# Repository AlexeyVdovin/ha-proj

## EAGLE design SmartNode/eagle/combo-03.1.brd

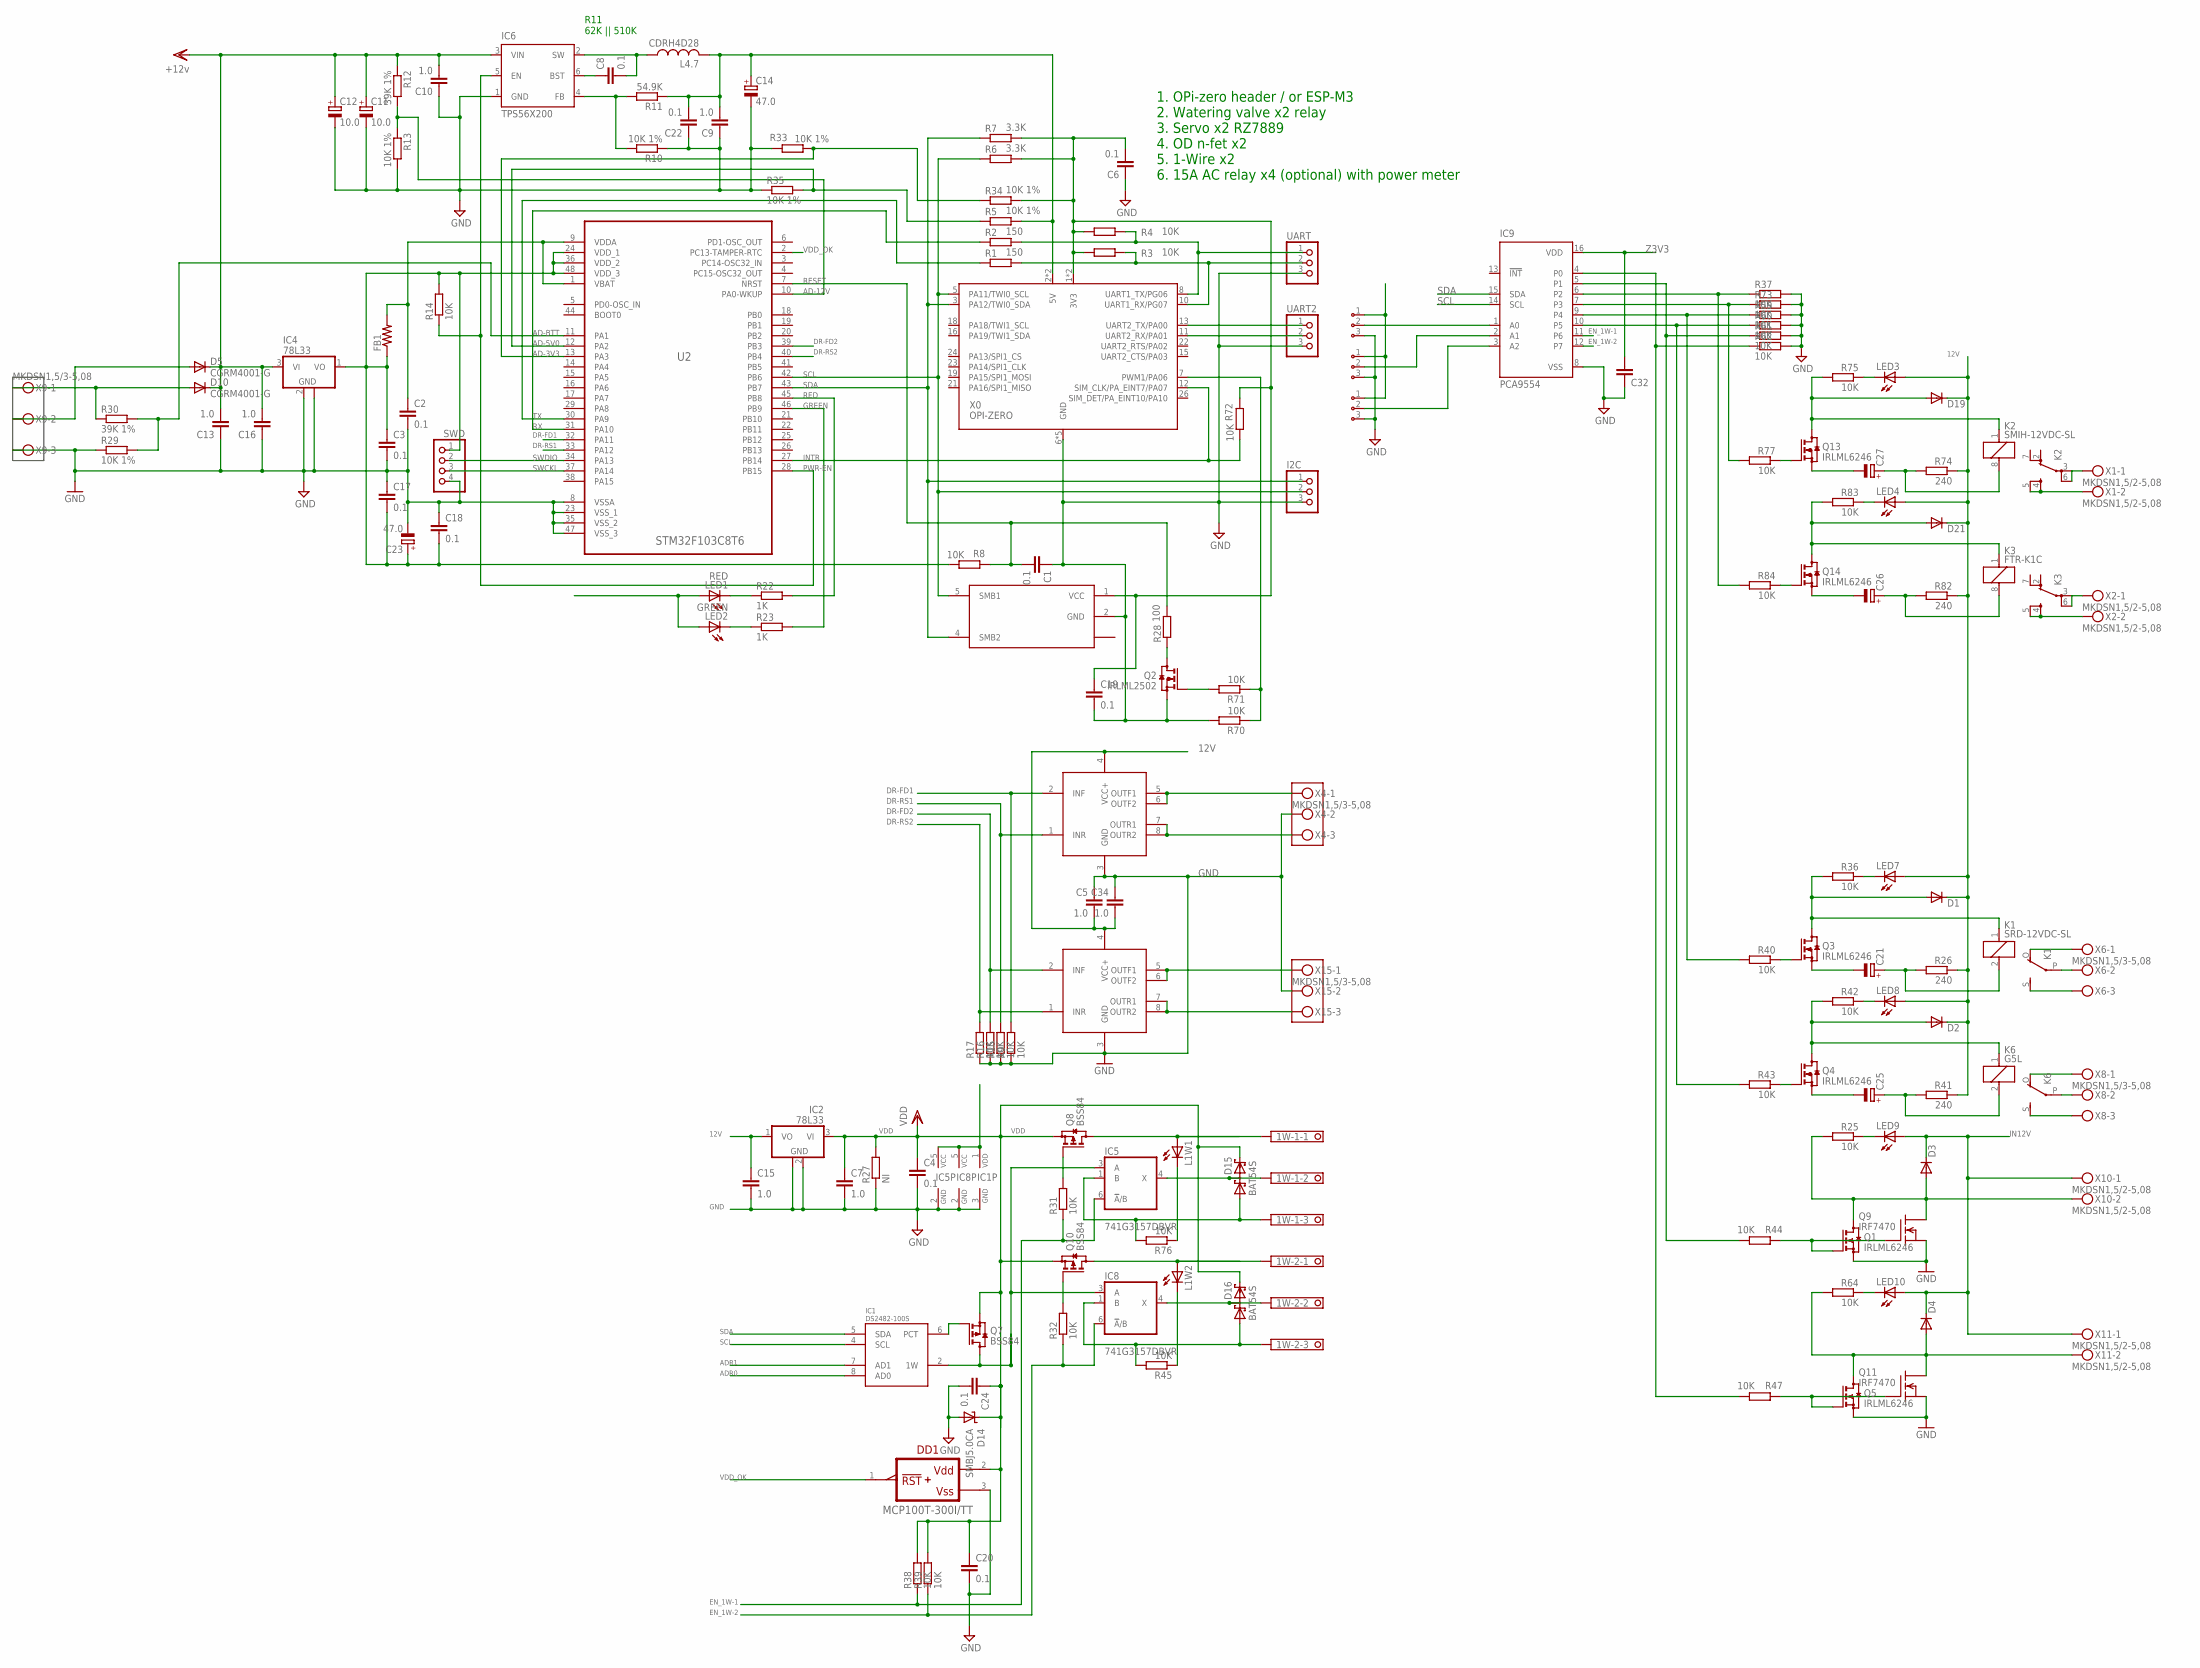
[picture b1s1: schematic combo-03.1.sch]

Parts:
1W-1, 1W-2: 1751251
A0, A1, A2: ADDR3PIN0603; 0603-3PIN
C1, C2, C3, C4, C17, C18, C19, C20, C24: 0.1; C0603
C5, C7, C9, C15, C34: 1.0; C0805
C6, C8, C22: 0.1; C0805
C10, C13, C16: 1.0; C1206
C11, C12: 10.0; C/6032-28R
C14, C23: 47.0; B/3528-21R
C21, C25, C26, C27: CPOL-EUE3.5-8; E3,5-8
C32: C-EUC0805; C0805
D1, D2, D3, D4, D19, D21: DIODE-SOD123; SOD123
D5, D10: CGRM4001-G; SOD-123_MINI-SMA
D14: SMBJ5.0CA; SMBJ
D15, D16: BAT54S; SOT23
DD1: MCP100T-300I/TT; SOT23
FB1: R-US_R0805; R0805
I2C: PINHD-1X3; 1X03
IC1: DS2482-100S; SO08
IC2, IC4: 78L33; SOT89
IC3, IC10: RZ7889; SO8
IC5, IC8: 741G3157DBVR; DBV_R-PDSO-G6
IC6: TPS56X200; TSOT23-6_DDC
IC7: LTC1694; SOT23-5
IC9: PCA9554; SO16W
K1: SRD-12VDC-SL; G5LE
K2: SMIH-12VDC-SL; FTR-K1C
K3: FTR-K1C
K6: G5L; G5LE
L1W1, L1W2: LEDSMT1206; 1206
L4.7: CDRH4D28
LED1: RED; CHIPLED_1206
LED2: GREEN; CHIPLED_1206
LED3, LED4, LED7, LED8, LED9, LED10: LEDSMT1206; 1206
Q1, Q3, Q4, Q5, Q13, Q14: IRLML6246; SOT23
Q2: IRLML2502; SOT23
Q7, Q8, Q10: BSS84; SOT23
Q9, Q11: IRF7470; SO-8
R1, R2: 150; R0603
R3, R4, R8, R9, R14, R15, R16, R17, R25, R31, R32, R36, R37, R38, R39, R40, R42, R43, R44, R45, R47, R59, R60, R61, R62, R64, R70, R71, R72, R73, R75, R76, R77, R83, R84: 10K; R0603
R5, R10, R13, R29, R33, R34, R35: 10K 1%; R0603
R6, R7: 3.3K; R0603
R11: 54.9K; R0603
R12, R30: 39K 1%; R0603
R22, R23: 1K; R0603
R26, R41, R74, R82: 240; R1206
R27: NI; R0603
R28: 100; R0603
SWD: PINHD-1X4; 1X04
U2: STM32F103C8T6; QFP50P900X900X160-48N
UART, UART2: PINHD-1X3; 1X03
X0: OPI-ZERO; OPI0
X1, X2, X10, X11: MKDSN1,5/2-5,08
X4, X6, X8, X9, X15: MKDSN1,5/3-5,08

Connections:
1W: IC1.2 (1W), IC5.3 (A), IC8.3 (A), Q7.3 (D)
1W1-VDD: 1W-1.1, L1W1.A, Q8.3 (D)
1W2-VDD: 1W-2.1, L1W2.A, Q10.3 (D)
12V: C5.2, C10.2, C11.+, C12.+, C13.2, C15.1, C16.2, C34.2, D1.C, D2.C, D5.C, D10.C, D19.C, D21.C, IC2.1 (VO), IC3.4 (VCC+), IC4.3 (VI), IC6.3 (VIN), IC10.4 (VCC+), LED3.A, LED4.A, LED7.A, LED8.A, R12.1, R26.1, R41.1, R74.1, R82.1
+3V3: C3.1, C17.2, C18.2, C23.+, FB1.1, IC4.1 (VO), R8.2, R14.2, SWD.1, U2.24 (VDD_1), U2.36 (VDD_2), U2.48 (VDD_3)
AD-3V3: R33.1, R34.1, U2.13 (PA3)
AD-5V0: R5.1, R35.2, U2.12 (PA2)
AD-12V: R12.2, R13.1, U2.10 (PA0-WKUP)
AD-BTT: R29.2, R30.2, U2.11 (PA1)
ADR0: A2.2, IC1.8 (AD0), IC9.1 (A0)
ADR1: A1.2, IC1.7 (AD1), IC9.2 (A1)
ADR2: A0.2, IC9.3 (A2)
BAT+: D10.A, R30.1, X9.1
DR-FD1: IC3.2 (INF), R9.2, U2.32 (PA11)
DR-FD2: IC10.2 (INF), R16.2, U2.39 (PB3)
DR-RS1: IC3.1 (INR), R15.2, U2.33 (PA12)
DR-RS2: IC10.1 (INR), R17.2, U2.40 (PB4)
EN_1W-1: IC5.6 (!A!/B), IC9.11 (P6), R31.1, R38.1
EN_1W-2: IC8.6 (!A!/B), IC9.12 (P7), R32.1, R39.1
FET: D3.A, Q1.3 (D), Q9.5 (D), Q9.6 (D), Q9.7 (D), Q9.8 (D), R25.2, X10.2
FET1: D4.A, Q5.3 (D), Q11.5 (D), Q11.6 (D), Q11.7 (D), Q11.8 (D), R64.2, X11.2
FR1: IC3.5 (OUTF1), IC3.6 (OUTF2), X4.1
FR2: IC10.5 (OUTF1), IC10.6 (OUTF2), X15.1
GND: 1W-1.3, 1W-2.3, A0.3, A1.3, A2.3, C1.1, C2.2, C3.2, C4.2, C5.1, C6.1, C7.2, C9.1, C10.1, C11.-, C12.-, C13.1, C14.-, C15.2, C16.1, C17.1, C18.1, C19.2, C20.2, C21.-, C22.1, C23.-, C24.2, C25.-, C26.-, C27.-, C32.1, C34.1, D14.A, D15.1 (A1), D16.1 (A1), DD1.3 (VSS), I2C.3, IC1.3 (GND), IC2.2 (GND), IC2.2@1 (GND), IC3.3 (GND), IC4.2 (GND), IC4.2@1 (GND), IC5.1 (B), IC5.2 (GND), IC6.1 (GND), IC7.2 (GND), IC8.1 (B), IC8.2 (GND), IC9.8 (VSS), IC10.3 (GND), Q1.2 (S), Q2.2 (S), Q3.2 (S), Q4.2 (S), Q5.2 (S), Q9.1 (S), Q9.2 (S), Q9.3 (S), Q11.1 (S), Q11.2 (S), Q11.3 (S), Q13.2 (S), Q14.2 (S), R9.1, R10.1, R13.2, R15.1, R16.1, R17.1, R27.1, R29.1, R33.2, R35.1, R37.2, R45.2, R59.2, R60.2, R61.2, R62.2, R70.2, R73.2, R76.2, SWD.4, U2.8 (VSSA), U2.23 (VSS_1), U2.35 (VSS_2), U2.47 (VSS_3), UART.3, UART2.3, X0.6 (GND), X0.9 (GND), X0.14 (GND), X0.20 (GND), X0.25 (GND), X4.2, X9.3, X15.2
GPIO1: IC9.9 (P4), R40.2, R59.1
GPIO2: IC9.10 (P5), R43.2, R60.1
GPIO4: IC9.7 (P3), R73.1, R77.2
GREEN: R23.2, U2.46 (PB9)
IN12V: D3.C, D4.C, D5.A, LED9.A, LED10.A, X9.2, X10.1, X11.1
INTR: R72.2, U2.27 (PB14), X0.12 (SIM_CLK/PA_EINT7/PA07)
IO13: IC9.5 (P1), R44.2, R61.1
unnamed: K3.4 (SA), K3.5 (SB), X2.2
unnamed: C8.2, IC6.2 (SW), L4.7.P$1 (1)
unnamed: Q2.3 (D), R28.1
unnamed: Q2.1 (G), R71.2
unnamed: IC9.6 (P2), R37.1, R84.2
unnamed: Q1.1 (G), Q9.4 (G), R44.1
unnamed: IC1.6 (PCT), Q7.1 (G)
unnamed: Q14.1 (G), R84.1
unnamed: D1.A, K1.1, Q3.3 (D), R36.2
unnamed: C21.+, K1.2, R26.2
unnamed: C8.1, IC6.6 (BST)
unnamed: LED7.C, R36.1
unnamed: Q3.1 (G), R40.1
unnamed: D2.A, K6.1, Q4.3 (D), R42.2
unnamed: C25.+, K6.2, R41.2
unnamed: IC6.4 (FB), R10.2, R11.2
unnamed: LED8.C, R42.1
unnamed: Q4.1 (G), R43.1
unnamed: 1W-1.2, D15.3 (C1A2), IC5.4 (X)
unnamed: Q8.1 (G), R31.2
unnamed: IC9.4 (P0), R47.2, R62.1
unnamed: K3.3 (PA), K3.6 (PB), X2.1
unnamed: 1W-2.2, D16.3 (C1A2), IC8.4 (X)
unnamed: Q10.1 (G), R32.2
unnamed: K1.P, X6.2
unnamed: K6.P, X8.2
unnamed: D19.A, K2.1, Q13.3 (D), R75.2
unnamed: C27.+, K2.8 (2), R74.2
unnamed: LED3.C, R75.1
unnamed: Q5.1 (G), Q11.4 (G), R47.1
unnamed: LED10.C, R64.1
unnamed: LED9.C, R25.1
unnamed: LED1.C, R22.1
unnamed: D21.A, K3.1, Q14.3 (D), R83.2
unnamed: Q13.1 (G), R77.1
unnamed: L1W2.C, R45.1
unnamed: L1W1.C, R76.1
unnamed: C26.+, K3.8 (2), R82.2
unnamed: LED4.C, R83.1
unnamed: LED2.C, R23.1
unnamed: K2.3 (PA), K2.6 (PB), X1.1
unnamed: K2.4 (SA), K2.5 (SB), X1.2
NC1: K1.O, X6.1
NC6: K6.O, X8.1
NO1: K1.S, X6.3
NO6: K6.S, X8.3
PA06: R70.1, R71.1, X0.7 (PWM1/PA06)
PWR-EN: IC6.5 (EN), R14.1, U2.28 (PB15)
RED: R22.2, U2.45 (PB8)
RESET: C1.2, R8.1, R28.2, U2.7 (NRST)
RS1: IC3.7 (OUTR1), IC3.8 (OUTR2), X4.3
RS2: IC10.7 (OUTR1), IC10.8 (OUTR2), X15.3
RX: R2.1, U2.31 (PA10)
SCL: I2C.2, IC1.4 (SCL), IC7.5 (SMB1), IC9.14 (SCL), R6.1, U2.42 (PB6), X0.5 (PA11/TWI0_SCL)
SDA: I2C.1, IC1.5 (SDA), IC7.4 (SMB2), IC9.15 (SDA), R7.1, U2.43 (PB7), X0.3 (PA12/TWI0_SDA)
SWCKL: SWD.3, U2.37 (PA14)
SWDIO: SWD.2, U2.34 (PA13)
TX: R1.1, U2.30 (PA9)
VDD: C4.1, C7.1, C20.1, C24.1, D14.C, D15.2 (C2), D16.2 (C2), DD1.2 (VDD), IC2.3 (VI), LED1.A, LED2.A, Q7.2 (S), Q8.2 (S), Q10.2 (S), R27.2, R38.2, R39.2
VDDA: C2.1, FB1.2, U2.1 (VBAT), U2.9 (VDDA)
VDD_OK: DD1.1 (!RST), U2.2 (PC13-TAMPER-RTC)
Z2RX: UART2.2, X0.11 (UART2_RX/PA01)
Z2TX: UART2.1, X0.13 (UART2_TX/PA00)
Z3V3: A0.1, A1.1, A2.1, C6.2, C19.1, C32.2, IC1.1 (VDD), IC5.5 (VCC), IC7.1 (VCC), IC8.5 (VCC), IC9.16 (VDD), R3.1, R4.1, R6.2, R7.2, R34.2, R72.1, X0.1 (3V3), X0.17 (3V3)
Z5V: C9.2, C14.+, C22.2, L4.7.P$2 (2), R5.2, R11.1, X0.2 (5V), X0.4 (5V)
ZRX: R1.2, R3.2, UART.2, X0.10 (UART1_RX/PG07)
ZTX: R2.2, R4.2, UART.1, X0.8 (UART1_TX/PG06)

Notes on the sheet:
R11 62K || 510K
1. OPi-zero header / or ESP-M3 2. Watering valve x2 relay 3. Servo x2 RZ7889 4. OD n-fet x2 5. 1-Wire x2 6. 15A AC relay x4 (optional) with power meter

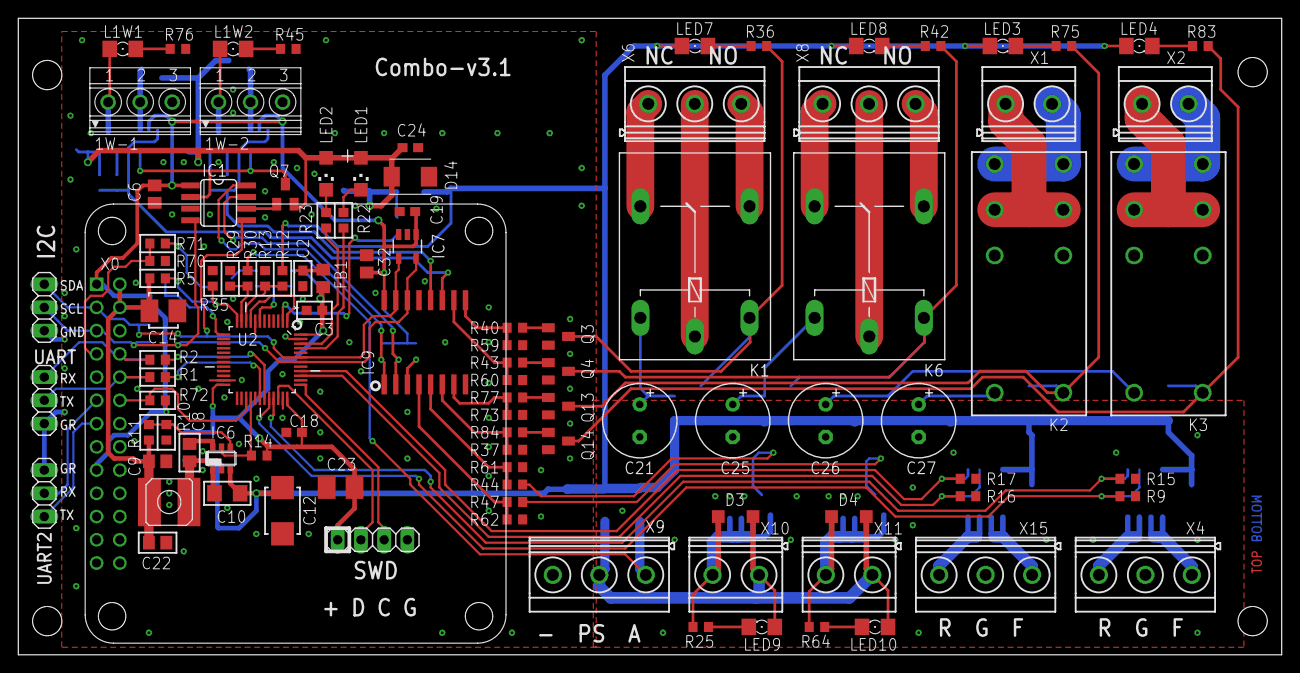
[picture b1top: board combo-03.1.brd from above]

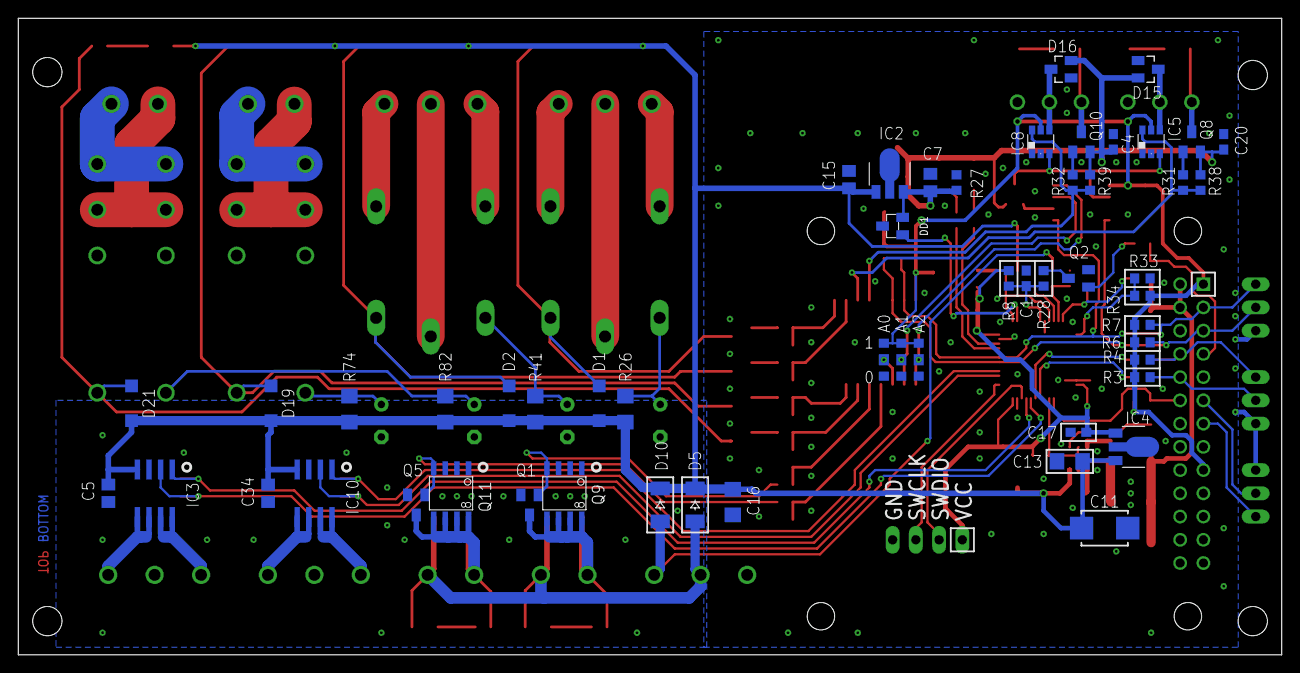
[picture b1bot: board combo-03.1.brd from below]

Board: 2 copper layers, 138.1 x 69.6 mm, 156 parts (53 on the bottom side), 98 nets.

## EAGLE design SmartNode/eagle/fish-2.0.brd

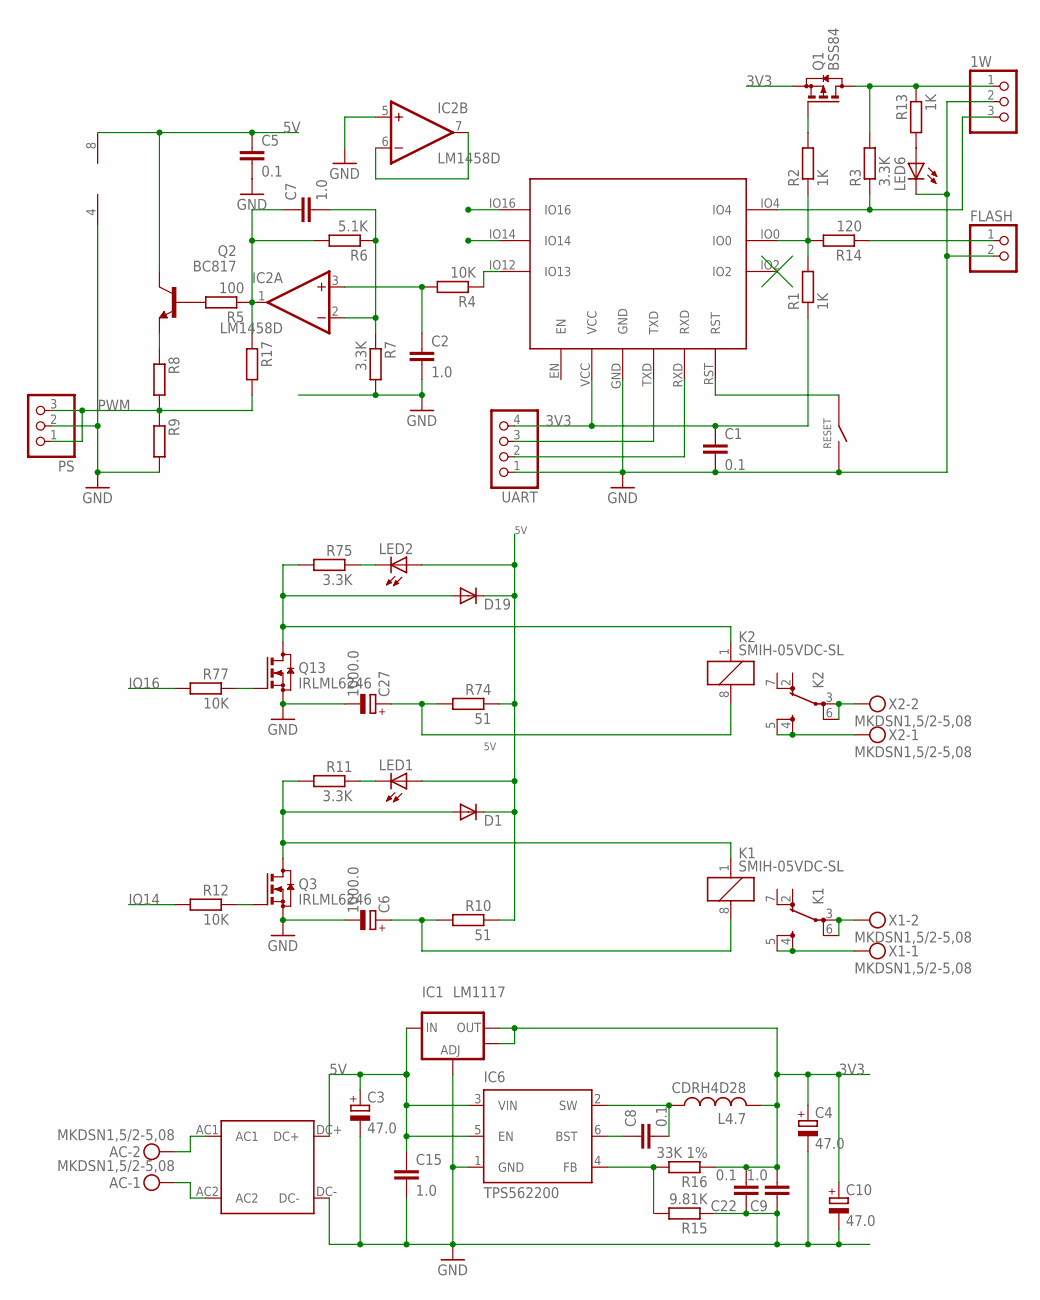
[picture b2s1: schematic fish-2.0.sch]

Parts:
1W: PINHD-1X3/90; 1X03/90
AC: MKDSN1,5/2-5,08
C1, C5, C8, C22: 0.1; C0805
C2, C7, C9, C15: 1.0; C0805
C3, C10: 47.0; SMC_D
C4: 47.0; SMC_B
C6, C27: 1000.0; E3,5-8
D1, D19: DIODE-SOD123; SOD123
ESP-M3: ESP-M3
FLASH: PINHD-1X2/90; 1X02/90
IC1: LM1117; SOT223
IC2: LM1458D; SO08
IC6: TPS562200; TSOT23-6_DDC
K1, K2: SMIH-05VDC-SL; FTR-K1C
L4.7: CDRH4D28
LED1, LED2, LED6: LEDSMT1206; 1206
PS: PINHD-1X3/90; 1X03/90
Q1: BSS84; SOT23
Q2: BC817; SOT23-BEC
Q3, Q13: IRLML6246; SOT23
R1, R2, R13: 1K; R0603
R3, R7, R11, R75: 3.3K; R0603
R4, R12, R77: 10K; R0603
R5: 100; R0603
R6: 5.1K; R0603
R8, R9, R17: R-EU_R0603; R0603
R10, R74: 51; R1206
R14: 120; R0603
R15: 9.81K; R0603
R16: 33K 1%; R0603
RESET: TACT3X4
U$1: AC-DC/10W-12V; AC-DC/10W
UART: PINHD-1X4/90; 1X04/90
X1, X2: MKDSN1,5/2-5,08

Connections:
1W: 1W.3, ESP-M3.IO4, R3.1
3V3: C1.1, C4.+, C9.2, C10.+, C22.2, ESP-M3.VCC, IC1.2 (OUT), IC1.4 (OUT), L4.7.P$2 (2), Q1.2 (S), R1.1, R16.1, UART.4
5V: C3.+, C5.1, C15.1, D1.C, D19.C, IC1.3 (IN), IC2.8 (V+), IC6.3 (VIN), IC6.5 (EN), LED1.A, LED2.A, Q2.C, R10.1, R74.1, U$1.DC+
BOOT: C8.1, IC6.6 (BST)
FB: IC6.4 (FB), R15.2, R16.2
FLASH: FLASH.1, R14.1
GND: 1W.2, C1.2, C2.2, C3.-, C4.-, C5.2, C6.-, C9.1, C10.-, C15.2, C22.1, C27.-, ESP-M3.GND, FLASH.2, IC1.1 (ADJ), IC2.4 (V-), IC2.5 (+IN), IC6.1 (GND), LED6.C, PS.2, Q3.2 (S), Q13.2 (S), R7.2, R9.2, R15.1, RESET.P$2, U$1.DC-, UART.1
IO14: ESP-M3.IO14, R12.2
IO16: ESP-M3.IO16, R77.2
unnamed: Q1.1 (G), R2.2
unnamed: AC.2, U$1.AC1
unnamed: ESP-M3.IO12 (IO13), R4.1
unnamed: AC.1, U$1.AC2
unnamed: C2.1, IC2.3 (+IN), R4.2
unnamed: C7.1, IC2.1 (OUT), R5.1, R6.2, R17.1
unnamed: C7.2, IC2.2 (-IN), R6.1, R7.1
unnamed: D1.A, K1.1, Q3.3 (D), R11.2
unnamed: Q2.B, R5.2
unnamed: Q2.E, R8.1
unnamed: C6.+, K1.8 (2), R10.2
unnamed: LED1.C, R11.1
unnamed: Q3.1 (G), R12.1
unnamed: K1.3 (PA), K1.6 (PB), X1.2
unnamed: ESP-M3.IO0, R1.2, R2.1, R14.2
unnamed: LED6.A, R13.2
unnamed: IC2.6 (-IN), IC2.7 (OUT)
unnamed: K1.4 (SA), K1.5 (SB), X1.1
unnamed: D19.A, K2.1, Q13.3 (D), R75.2
unnamed: C27.+, K2.8 (2), R74.2
unnamed: LED2.C, R75.1
unnamed: Q13.1 (G), R77.1
unnamed: K2.3 (PA), K2.6 (PB), X2.2
unnamed: K2.4 (SA), K2.5 (SB), X2.1
PWM: PS.1, PS.3, R8.2, R9.1, R17.2
RST: ESP-M3.RST, RESET.P$1
RX1: ESP-M3.RXD, UART.2
SW: C8.2, IC6.2 (SW), L4.7.P$1 (1)
TX1: ESP-M3.TXD, UART.3
VCC: 1W.1, Q1.3 (D), R3.2, R13.1

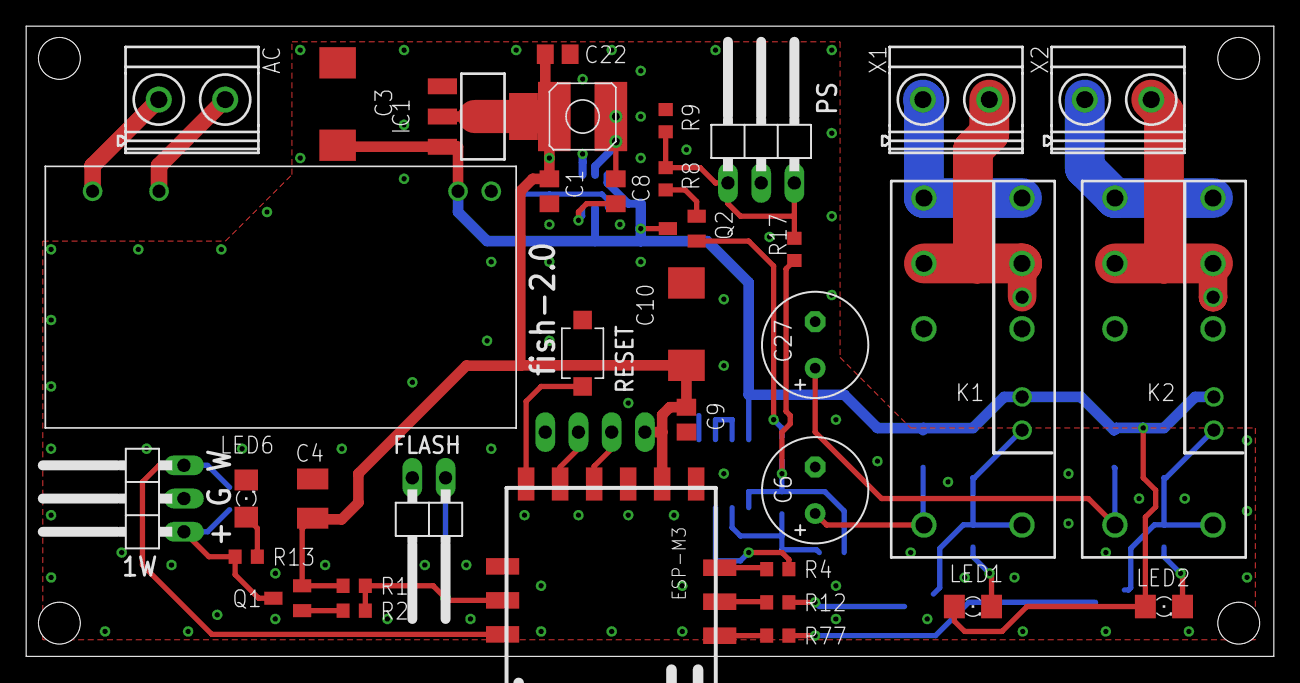
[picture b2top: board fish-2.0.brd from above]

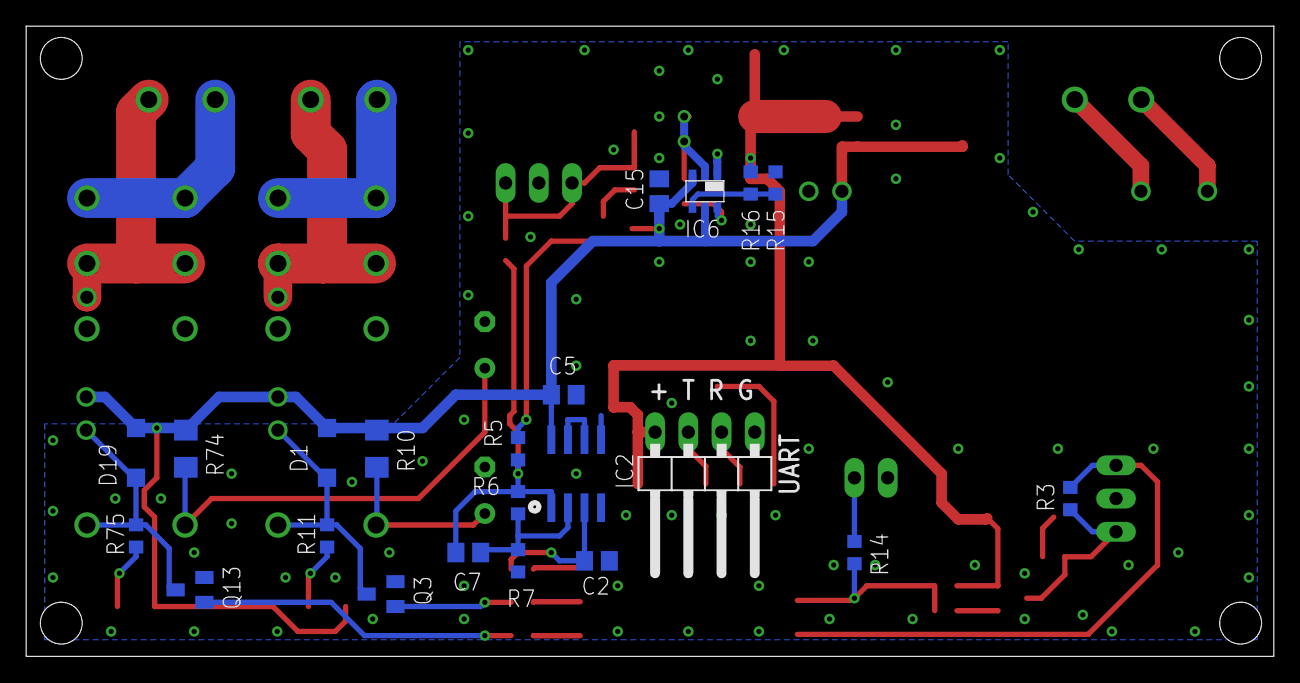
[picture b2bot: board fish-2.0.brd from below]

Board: 2 copper layers, 95.4 x 48.2 mm, 58 parts (22 on the bottom side), 39 nets.

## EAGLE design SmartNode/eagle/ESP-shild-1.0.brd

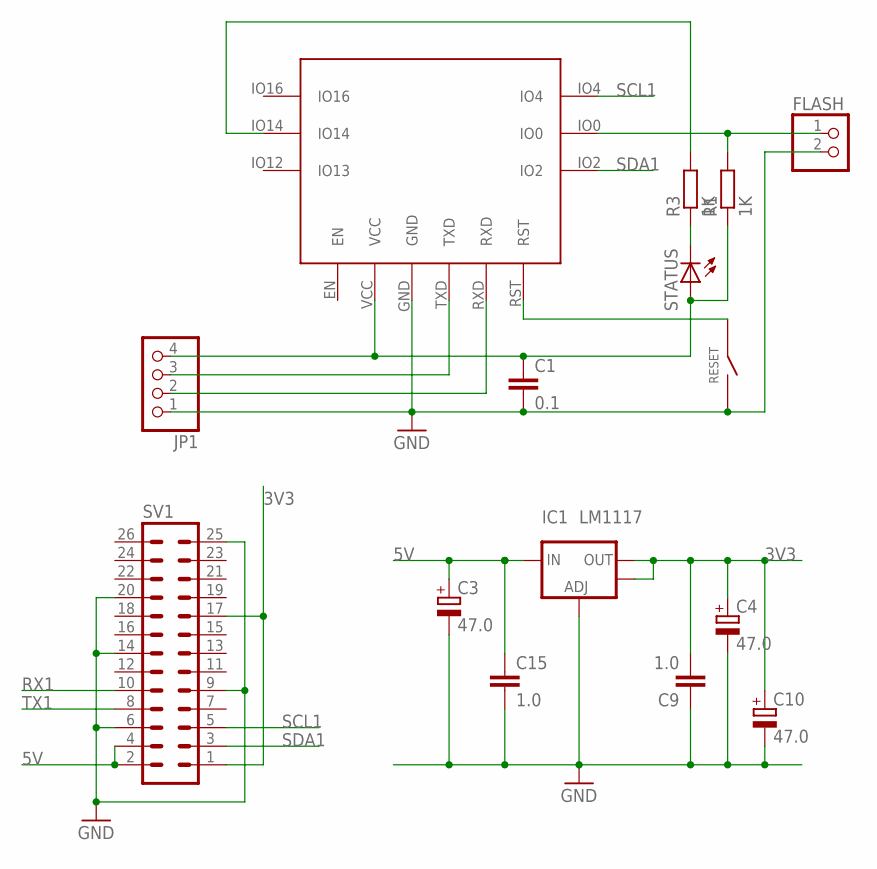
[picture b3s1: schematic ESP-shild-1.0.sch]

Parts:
C1: 0.1; C0805
C3, C10: 47.0; SMC_D
C4: 47.0; SMC_B
C9, C15: 1.0; C0805
ESP-M3: ESP-M3
FLASH: PINHD-1X2/90; 1X02/90
IC1: LM1117; SOT223
JP1: PINHD-1X4/90; 1X04/90
R1, R3: 1K; R0603
RESET: TACT3X4
STATUS: LEDSML1206; SML1206
SV1: MA13-2

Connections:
3V3: C1.1, C4.+, C9.2, C10.+, ESP-M3.VCC, IC1.2 (OUT), IC1.4 (OUT), JP1.4, R1.1, STATUS.A, SV1.1, SV1.17
5V: C3.+, C15.1, IC1.3 (IN), SV1.2, SV1.4
FLASH: ESP-M3.IO0, FLASH.1, R1.2
GND: C1.2, C3.-, C4.-, C9.1, C10.-, C15.2, ESP-M3.GND, FLASH.2, IC1.1 (ADJ), JP1.1, RESET.P$2, SV1.6, SV1.9, SV1.14, SV1.20, SV1.25
LED: ESP-M3.IO14, R3.2
unnamed: R3.1, STATUS.C
RST: ESP-M3.RST, RESET.P$1
RX1: ESP-M3.RXD, JP1.2, SV1.10
SCL1: ESP-M3.IO4, SV1.5
SDA1: ESP-M3.IO2, SV1.3
TX1: ESP-M3.TXD, JP1.3, SV1.8

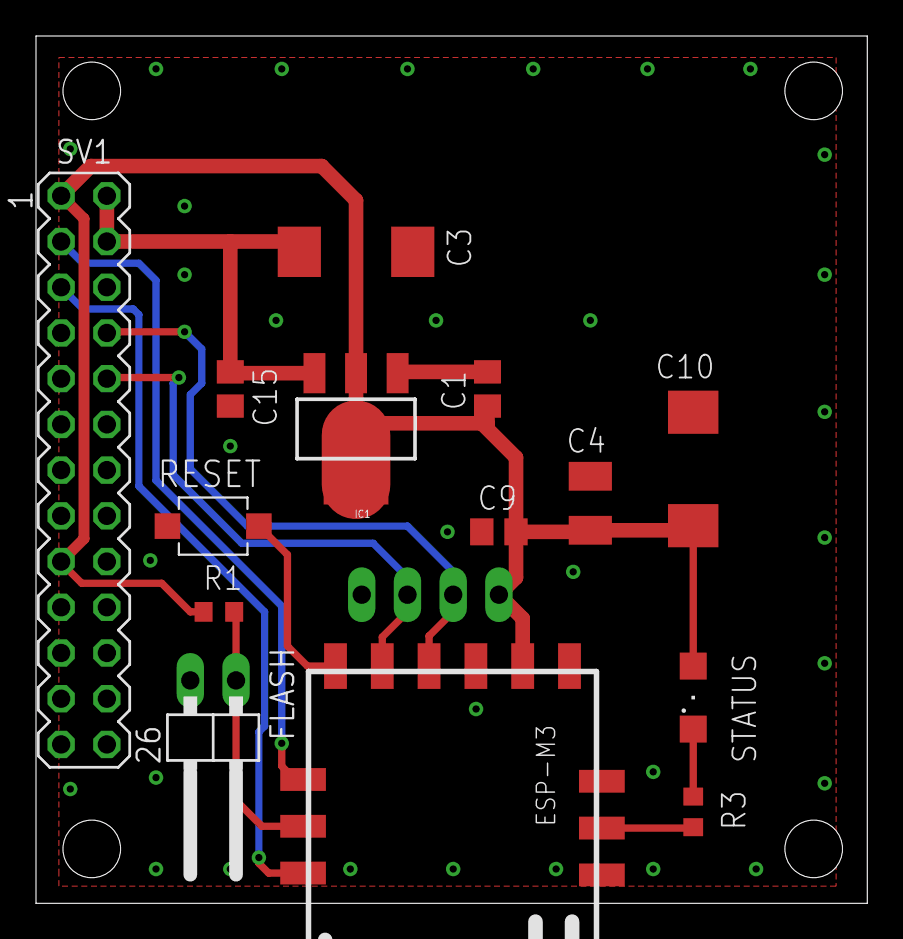
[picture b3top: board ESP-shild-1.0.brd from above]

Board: 2 copper layers, 46.2 x 48.2 mm, 15 parts (1 on the bottom side), 11 nets.

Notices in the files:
parts and their libraries:
SparkFun: Licensing: CC v3.0 Share-Alike You are welcome to use this library for commercial purposes.
